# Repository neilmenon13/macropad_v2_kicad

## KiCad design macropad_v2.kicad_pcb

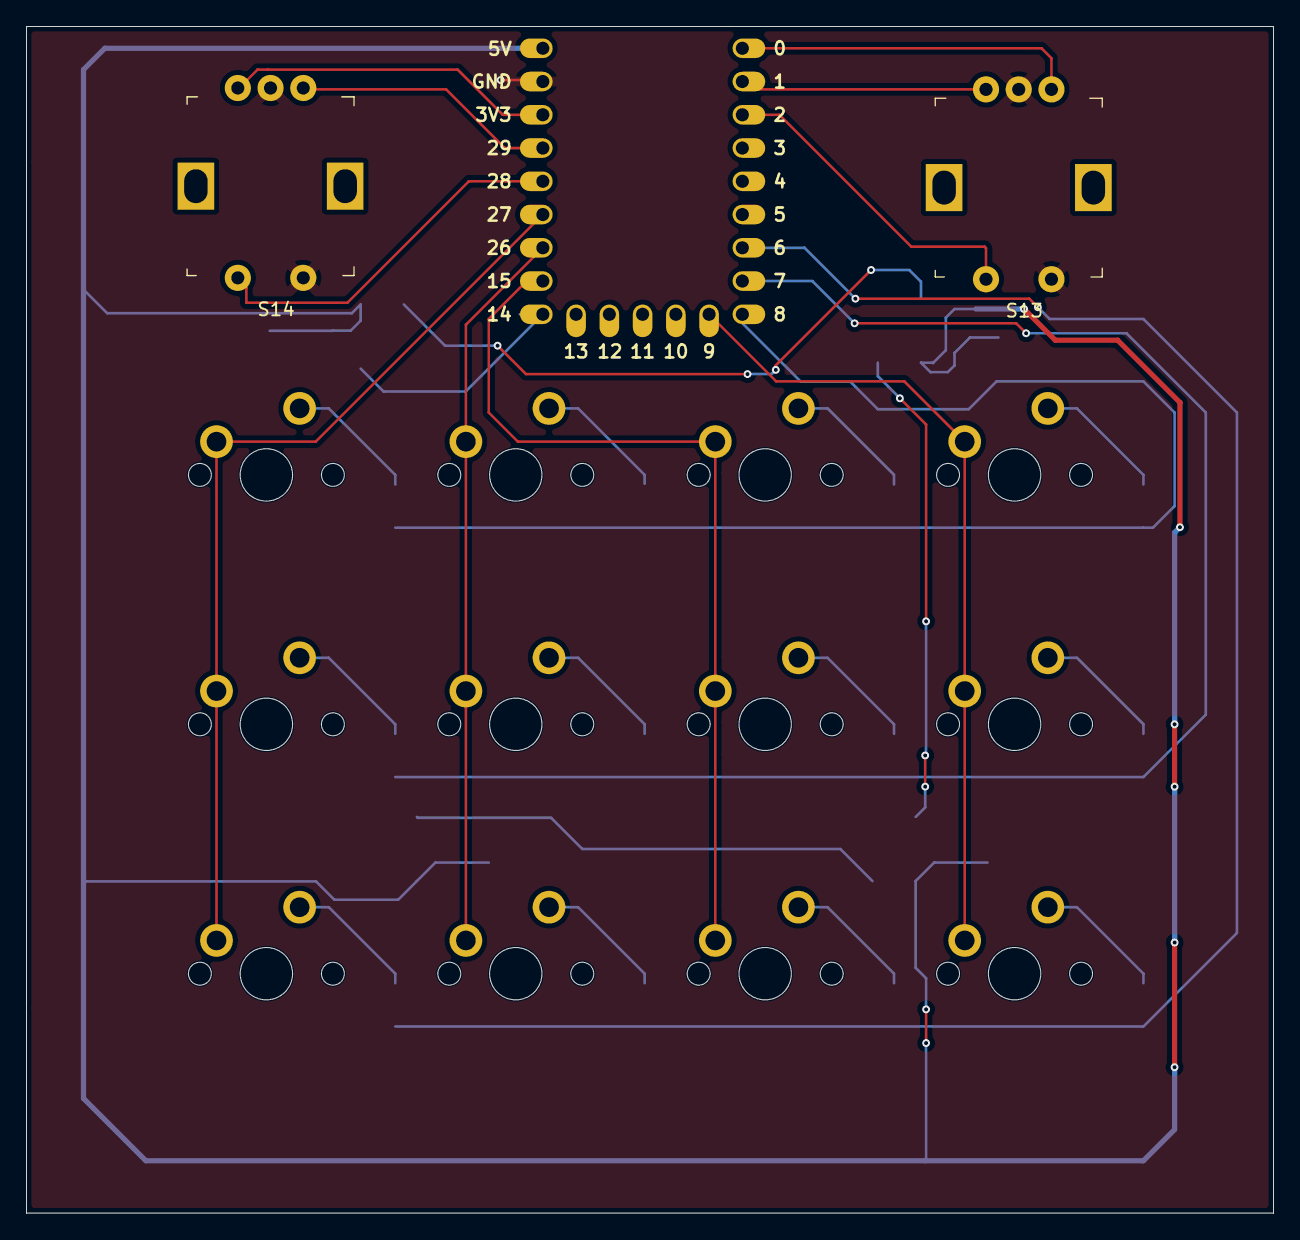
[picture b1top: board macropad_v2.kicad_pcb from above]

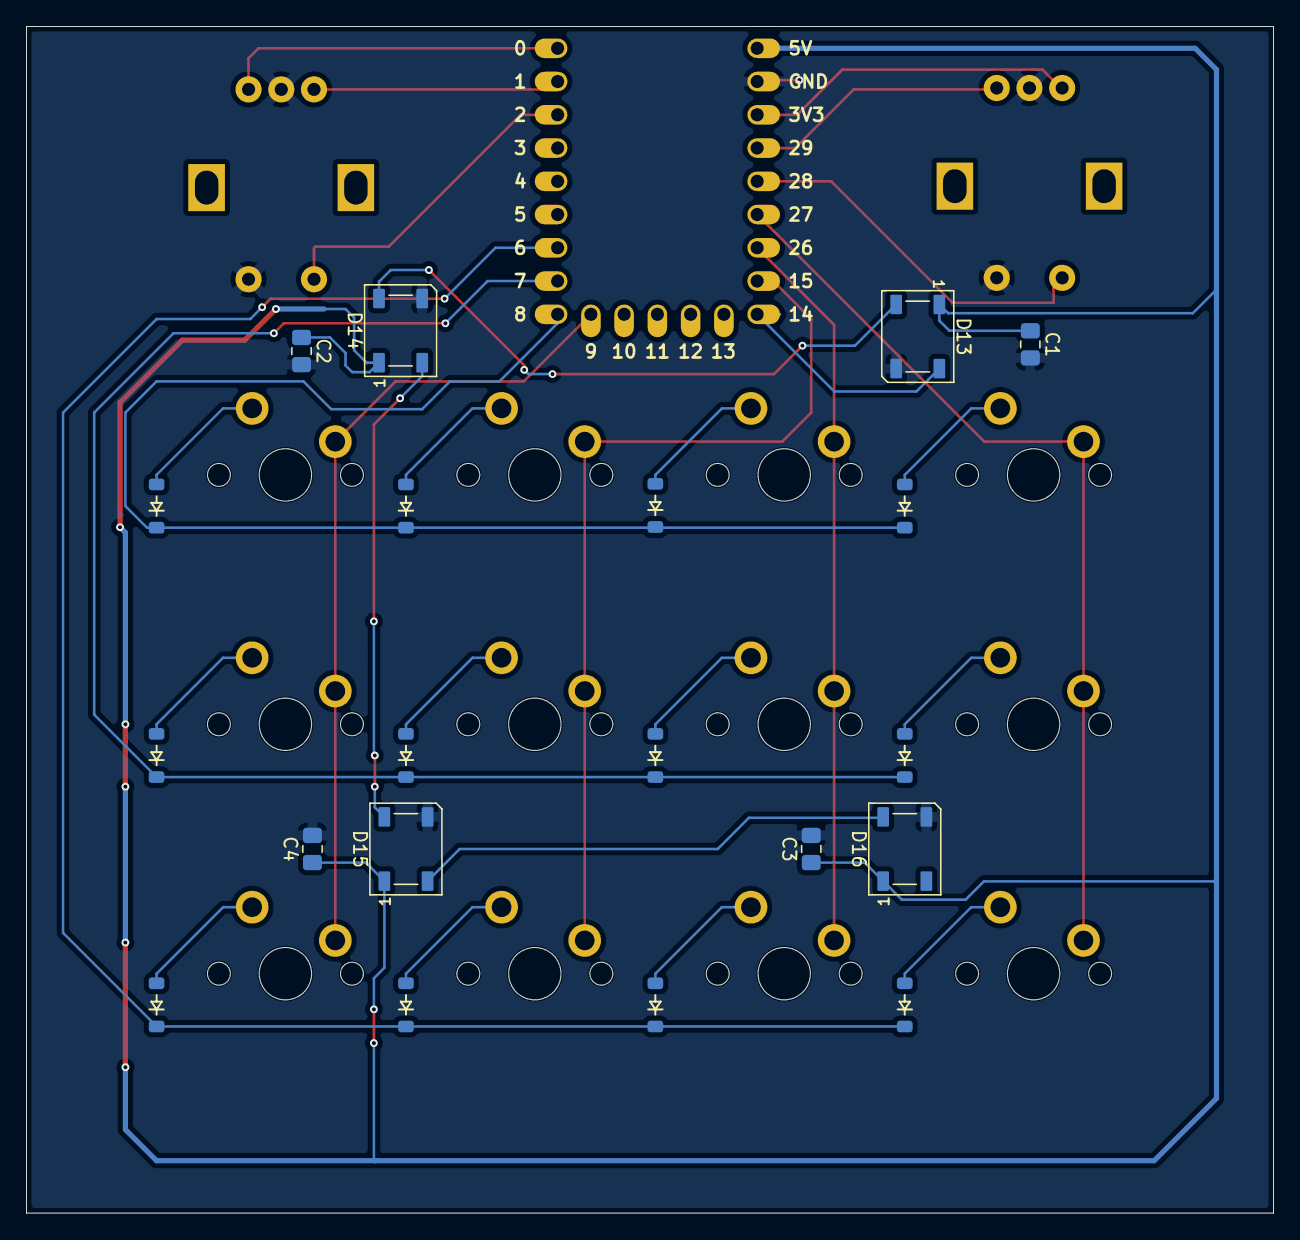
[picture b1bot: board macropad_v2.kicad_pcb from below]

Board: 2 copper layers, 95.3 x 90.6 mm, 35 parts (20 on the bottom side), 31 nets.

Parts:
C1, C2, C3, C4: C; C_0805_2012Metric_Pad1.18x1.45mm_HandSolder
D1, D2, D3, D4, D5, D6, D7, D8, D9, D10, D11, D12: Diode_SOD-123
D13, D14, D15, D16: WS2812B; LED_WS2812B_PLCC4_5.0x5.0mm_P3.2mm
S1, S2, S3, S4, S5, S6, S7, S8, S9, S10, S11, S12: MX_Solder_1.00u
S13, S14: PEC11R-4215F-S0024; Rotary_Encoder_Switched_PEC11R
U2: RP2040_Zero

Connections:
+5V: C1.1, C2.1, C3.1, C4.1, D13.1 (VDD), D14.1 (VDD), D15.1 (VDD), D16.1 (VDD), U2.23 (5V)
/COL 0: S1.1, S5.1, S9.1, U2.18 (27)
/COL 1: S2.1, S6.1, S10.1, U2.17 (26)
/COL 2: S3.1, S7.1, S11.1, U2.16 (15)
/COL 3: S4.1, S8.1, S12.1, U2.10 (9)
/ENC_A: S13.A (CH_A), U2.1 (0)
/ENC_A_2: S14.A (CH_A), U2.20 (29)
/ENC_B: S13.B (CH_B), U2.2 (1)
/ENC_B_2: S14.B (CH_B), U2.21 (3V3)
/ENC_SW: S13.2, U2.3 (2)
/ENC_SW_2: S14.2, U2.19 (28)
/RGB_DATA: D13.4 (DIN), U2.15 (14)
/ROW 0: D1.1 (K), D2.1 (K), D3.1 (K), D4.1 (K), U2.9 (8)
/ROW 1: D5.1 (K), D6.1 (K), D7.1 (K), D8.1 (K), U2.8 (7)
/ROW 2: D9.1 (K), D10.1 (K), D11.1 (K), D12.1 (K), U2.7 (6)
GND: C1.2, C2.2, C3.2, C4.2, D13.3 (VSS), D14.3 (VSS), D15.3 (VSS), D16.3 (VSS), S13.1, S13.C (COM), S14.1, S14.C (COM), U2.22 (GND)
unnamed: D1.2 (A), S1.2
unnamed: D2.2 (A), S2.2
unnamed: D3.2 (A), S3.2
unnamed: D4.2 (A), S4.2
unnamed: D5.2 (A), S5.2
unnamed: D6.2 (A), S6.2
unnamed: D7.2 (A), S7.2
unnamed: D8.2 (A), S8.2
unnamed: D9.2 (A), S9.2
unnamed: D10.2 (A), S10.2
unnamed: D11.2 (A), S11.2
unnamed: D12.2 (A), S12.2
unnamed: D13.2 (DOUT), D14.4 (DIN)
unnamed: D14.2 (DOUT), D15.4 (DIN)
unnamed: D15.2 (DOUT), D16.4 (DIN)
